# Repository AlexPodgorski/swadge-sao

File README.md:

# CR123A SAO

This is an evaluation board to test the viability of using LiMnO2 CR123A cells in a 1P3S configuration on the Swadge.

Attendees are reporting that their Swadges are too heavy. This is largely due to the 3xAA batteries, 24g each, used to power the Swadge in a 1P3S configuration. Batteries were evaluated, and CR123A batteries were selected for further evaluation on the SAO. They weigh in at 17g each.

CR123A are non-rechargeable, Lithium Chemistry batteries commonly used in camera and firearm accessory applications. They have a higher C rating than other traditional batteries (thanks to the Lithium Chemistry) and are safer than a traditional Lithium Ion or Lithium Polymer rechargeable battery. They maintain a steady voltage level of ~2.9V and discharge curves suggest approximately a 12hr battery life at 100mA continuous draw.

Preliminary testing showed:
1. Big Bug was pulling ~225mA
2. Swadge hero ~90% brightness with light show ~100mA
3. Main menu ~90mA-100mA

This is with the MT3410 + 5V USB input. 225mA at 5V is a whopping 1.125W. If we assume that same power draw and change to a 1P3S 9.0V source, we should expect to see 125mA draw (1.125W/9.0V) from the 3 cells.

The MT3410 does not support inputs above 6V, so a new DC-DC converter needed to be specified. XIAN Aerosemi Tech has other PMICs for higher voltages; the most affordable one appropriate for our use case is the <a href="https://www.lcsc.com/datasheet/lcsc_datasheet_2408140941_XI-AN-Aerosemi-Tech-MT2492_C89358.pdf">MT2492</a>. 

The MT2492 operates at a different switching frequency than the MT2410. The MT2410 switches at 1.2MHz vs 600kHz at the MT2492. I have EMI concerns with this. Additionally, the manufacturer recommends upsizing the inductor under light load conditions (<100mA), which can also impact EMI. I dont know if this will be worse, but it will be different. Predicting its behavior will be hard, so Im just going to send it on this SAO and see what happens. I have broken out the inductor pads such that I can easily drop in a new one if Id like to evaluate different values or if I need to probe something. I started with 4.7uH.

A lower switching frequency may be more efficient; I reviewed some <a href="https://www.ti.com/lit/an/slvaed3a/slvaed3a.pdf?ts=1744087588249&ref_url=https%253A%252F%252Fwww.google.com%252F"> documentation from TI </a> discussing how switching frequency impacts the performance of a buck converter. TI offers a device with adjustable switching frequency between 600kHz and 1MHz, and showed that at all loads, the 600kHz configuration ran cooler and saw ~85% efficiency vs 70% at loads we typically see in the Swadge. This is fairly device specific, but comparison of the Aerosemi datasheets suggests a higher efficiency as well with the 600kHz chip. Frankly, the plots on the datasheets are horrible and make drawing conclusions difficult. The MT2492 datasheet suggests that efficiency of the IC is around 95% at 9V/1A, and efficiency drops to around 93% at lower loads (~200mA). The MT2410 peaks at around 93% at 5V/300mA, and floats around 85% at 200mA. So, I am expecting about an 8-10% increase in efficiency switching to the MT2492.

The drawback in switching to a 600kHz solution is the requirement to upsize capacitors and inductors, which increases PCB area required for the MT2492. Higher frequency switching converters perform better in transient testing, so the MT2492 may over/undershoot during transition states more than the MT3410 does; possibly 15mV more? This is why larger capacitors and inductors are required.

A shunt Diode is in parallel with each battery into the MT2492 circuit. This is the only battery management system on board. It is possible (but unwise) to put in the RCR123A batteries (rechargeable Lithium Ion) although they have the same form factor, as there is no individual cell monitoring on this board.

# Testing Plan

The testing plan for this SAO is in two phases.

First is to attach it to a Hot Dog and monitor current draw from the USB on the SAO. This is to accomplish two tasks:
1. Compare against the existing Swadge circuit to evaluate power efficiency and noise of this new voltage regulation circuit
2. Gather more benchmark data to evaluate the battery performance

The states to be evaluated are:

1. Idle on Main Menu at max LED and TFT brightness, no screensaver
2. Big Bug at max brightness, maximum volume, general gameplay for 30 minutes and logging current consumption approximately every 60 seconds
3. Colorchord at 7 gain, LED 8, Max Screen Brightness Rainbow
4. Stepwise 0-7 TFT brightness on Main Menu
5. Stepwise 0-8 LED brightness on Main Menu
6. UTTT Wireless Connect Menu at max LED and TFT brightness

In theory, this will help us characterize current draw in various Swadge modes and help estimate run time in hours.

Second is to install the batteries and:
1. Monitor and log voltage at the diode node to GND over time
2. Monitor and log cell voltage at each node to GND over time

This will discharge a few sets of CR123A batteries in a few different states to characterize their charge time and see if the cells are staying relatively balanced. The states evaluated will be:
1. Big Bug at max brightness, maximum volume, general gameplay
2. Idle on Main Menu at max LED and TFT brightness, no screensaver
3. UTTT Wireless Connect Menu at max LED and TFT brightness

Durations for these tasks will be chosen based on the results of the first set of tests.

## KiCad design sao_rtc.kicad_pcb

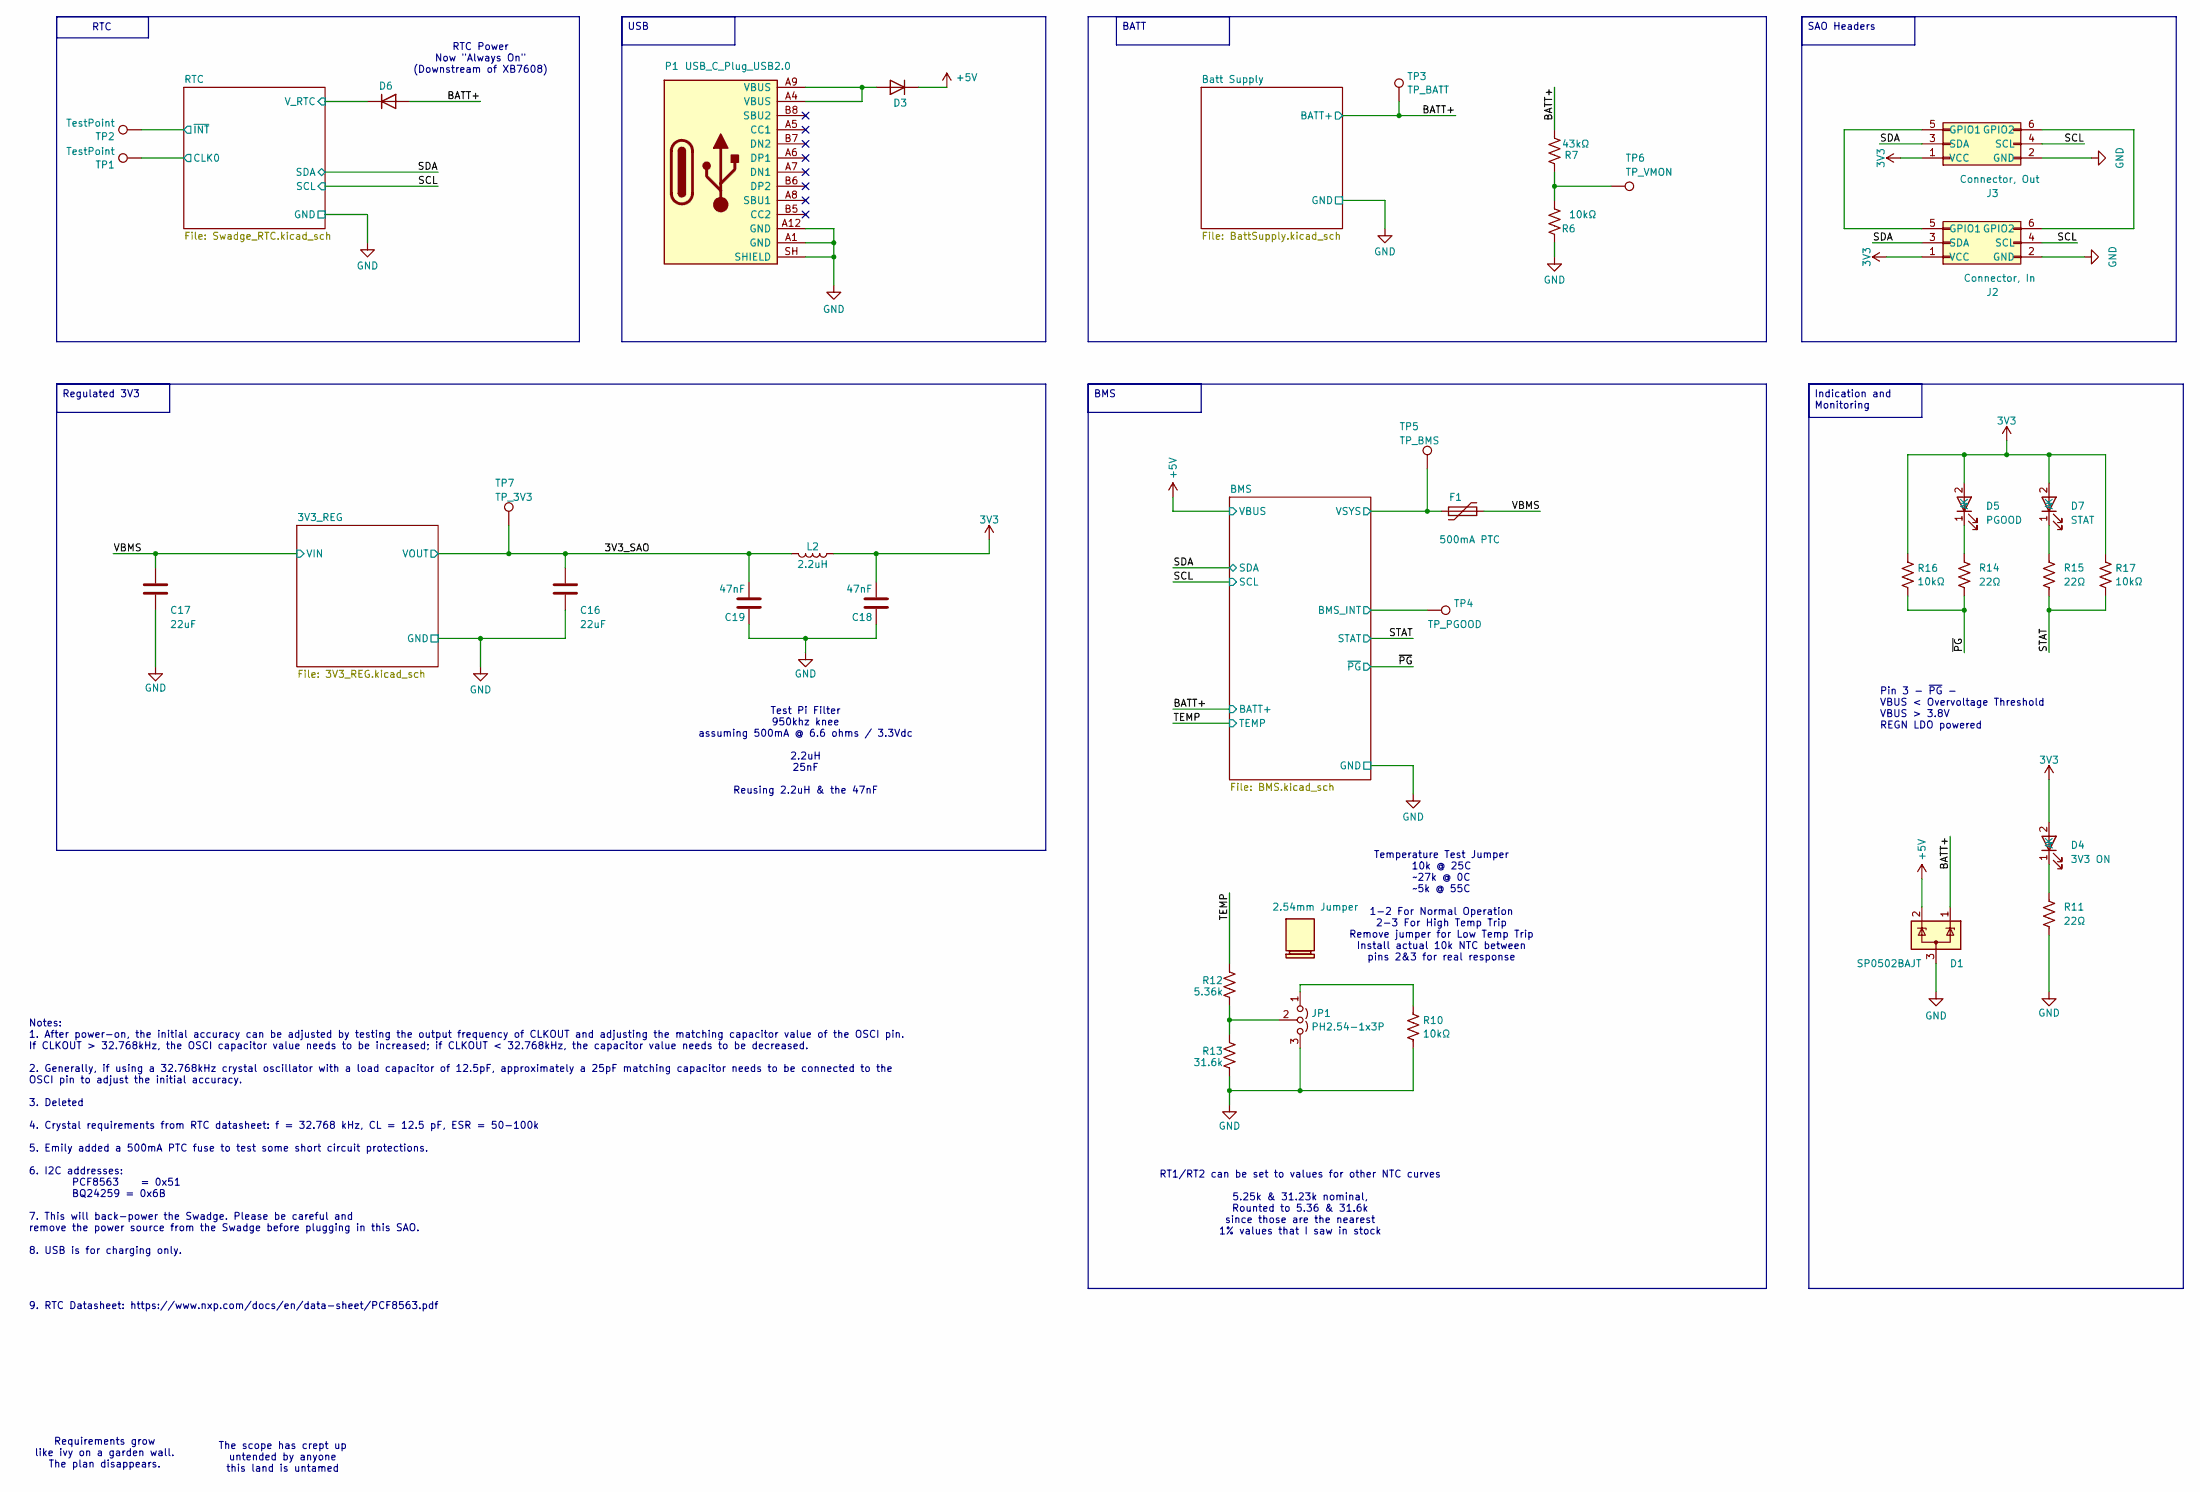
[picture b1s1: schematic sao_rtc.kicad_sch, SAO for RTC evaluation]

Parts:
C16, C17: 22uF; C_0603_1608Metric; LCSC C77042
C18, C19: 47nF; C_0603_1608Metric; LCSC C107093
D1: SP0502BAJT; SOT-323_SC-70; LCSC C207262
D3, D6: D; D_SMA; Digikey 2616-GS1J-ND
D4: 3V3 ON; LED_0603_1608Metric; LCSC C965804
D5: PGOOD; LED_0603_1608Metric; LCSC C965804
D7: STAT; LED_0603_1608Metric; LCSC C965804
F1: 500mA PTC; Fuse_0805_2012Metric
H1: 2.54mm Jumper; LCSC C5305
J2: Connector, In; PinHeader_2x03_P2.54mm_Vertical; LCSC C492420
J3: Connector, Out; PinHeader_2x03_P2.54mm_Vertical_Flipped; LCSC C541853
JP1: PH2.54-1x3P; PinHeader_1x03_P2.54mm_Vertical; LCSC C42431836
L2: 2.2uH; L_1008_2520Metric; LCSC C216158
P1: USB_C_Plug_USB2.0; USB_C_Receptacle_HRO_TYPE-C-31-M-12; LCSC C2765186
R6, R10, R16, R17: 10kΩ; R_0603_1608Metric; LCSC C25804
R7: 43kΩ; R_0603_1608Metric; LCSC C23172
R11, R14, R15: 22Ω; R_0603_1608Metric; LCSC C23345
R12: 5.36k; R_0603_1608Metric; LCSC C25973
R13: 31.6k; R_0603_1608Metric; LCSC 25967
TP1, TP2: TestPoint; TestPoint_Loop_D2.60mm_Drill1.4mm_Beaded; LCSC C5199801
TP3: TP_BATT; TestPoint_Loop_D2.60mm_Drill1.4mm_Beaded; LCSC C5199801
TP4: TP_PGOOD; TestPoint_Loop_D2.60mm_Drill1.4mm_Beaded; LCSC C5199801
TP5: TP_BMS; TestPoint_Loop_D2.60mm_Drill1.4mm_Beaded; LCSC C5199801
TP6: TP_VMON; TestPoint_Loop_D2.60mm_Drill1.4mm_Beaded; LCSC C5199801
TP7: TP_3V3; TestPoint_Loop_D2.60mm_Drill1.4mm_Beaded; LCSC C5199801

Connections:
3V3: C18.1, D4.2 (A), D5.2 (A), D7.2 (A), J2.1 (VCC), J3.1 (VCC), L2.1, R16.2, R17.2
+5V: D1.2 (K), D3.1 (K); also elsewhere on the board
/3V3_SAO: C16.1, C19.1, L2.2, TP7.1 (1_1); also elsewhere on the board
/BATT+: D1.1 (K), D6.2 (A), R7.2, TP3.1 (1_1); also elsewhere on the board
/BMS/BMS_INT: TP4.1 (1_1); also elsewhere on the board
/BMS/VSYS: F1.1, TP5.1 (1_1); also elsewhere on the board
/RTC/CLK0: TP1.1 (1_1); also elsewhere on the board
/RTC/V_RTC: D6.1 (K); also elsewhere on the board
/RTC/~INT: TP2.1 (1_1); also elsewhere on the board
/SCL: J2.4 (SCL), J3.4 (SCL); also elsewhere on the board
/SDA: J2.3 (SDA), J3.3 (SDA); also elsewhere on the board
/STAT: R15.1, R17.1; also elsewhere on the board
/TEMP: R12.1; also elsewhere on the board
/VBMS: C17.1, F1.2; also elsewhere on the board
/~PG: R14.1, R16.1; also elsewhere on the board
GND: C16.2, C17.2, C18.2, C19.2, D1.3 (A), J2.2 (GND), J3.2 (GND), JP1.3 (B), P1.A1 (GND), P1.A12 (GND), P1.SH (SHIELD), R6.2, R10.1, R11.1, R13.2; also elsewhere on the board
unnamed: D3.2 (A), P1.A4 (VBUS), P1.A9 (VBUS)
unnamed: D4.1 (K), R11.2
unnamed: D5.1 (K), R14.2
unnamed: D7.1 (K), R15.2
unnamed: J2.5 (GPIO1), J3.5 (GPIO1)
unnamed: J2.6 (GPIO2), J3.6 (GPIO2)
unnamed: JP1.1 (A), R10.2
unnamed: JP1.2 (C), R12.2, R13.1
unnamed: R6.1, R7.1, TP6.1 (1_1)

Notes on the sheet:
Test Pi Filter 950khz knee assuming 500mA @ 6.6 ohms / 3.3Vdc 2.2uH 25nF Reusing 2.2uH & the 47nF
The scope has crept up untended by anyone this land is untamed
RTC
Temperature Test Jumper 10k @ 25C ~27k @ 0C ~5k @ 55C 1-2 For Normal Operation 2-3 For High Temp Trip Remove jumper for Low Temp Trip Install actual 10k NTC between pins 2&3 for real response
RT1/RT2 can be set to values for other NTC curves 5.25k & 31.23k nominal, Rounted to 5.36 & 31.6k since those are the nearest 1% values that I saw in stock
Requirements grow like ivy on a garden wall. The plan disappears.
9. RTC Datasheet: https://www.nxp.com/docs/en/data-sheet/PCF8563.pdf
Notes: 1. After power-on, the initial accuracy can be adjusted by testing the output frequency of CLKOUT and adjusting the matching capacitor value of the OSCI pin. If CLKOUT > 32.768kHz, the OSCI capacitor value needs to be increased; if CLKOUT < 32.768kHz, the capacitor value needs to be decrease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
Pin 3 - ~{PG} - VBUS < Overvoltage Threshold VBUS > 3.8V REGN LDO powered
RTC Power Now "Always On" (Downstream of XB7608)
SAO Headers
BATT
BMS
USB
Indication and Monitoring
Regulated 3V3

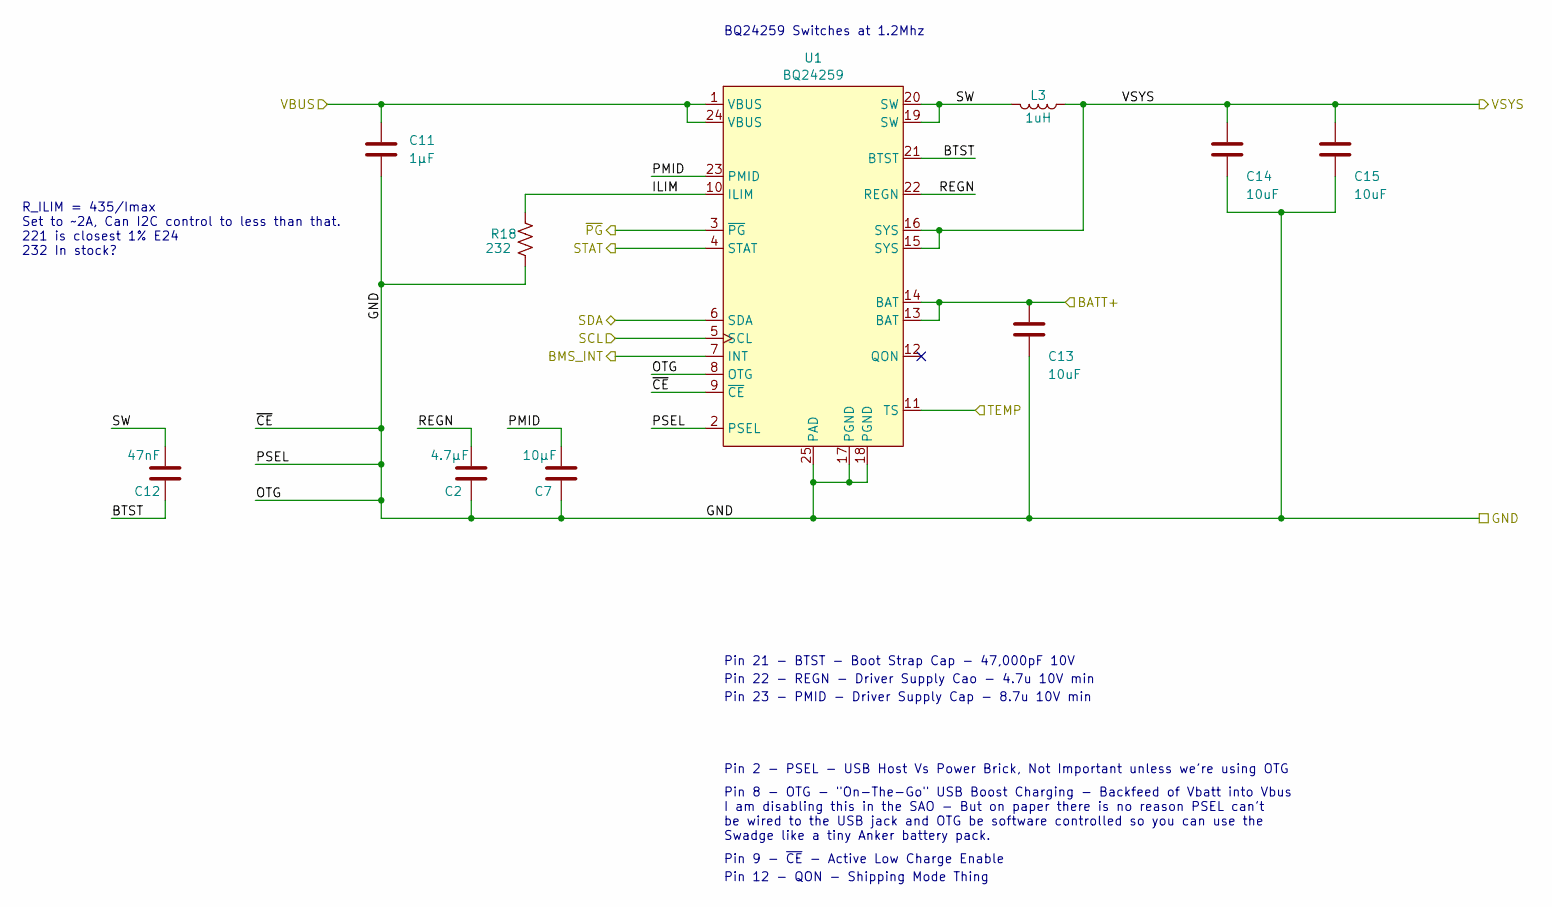
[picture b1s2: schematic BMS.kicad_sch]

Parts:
C2: 4.7μF; C_0603_1608Metric; LCSC C1705
C7: 10μF; C_0603_1608Metric; LCSC C85713
C11: 1μF; C_0603_1608Metric; LCSC C159801
C12: 47nF; C_0603_1608Metric; LCSC C107093
C13, C14, C15: 10uF; C_0603_1608Metric; LCSC C1691
L3: 1uH; L_1008_2520Metric; LCSC C48996586
R18: 232; R_0603_1608Metric; LCSC C23009
U1: BQ24259; HVQFN-24-1EP_4x4mm_P0.5mm_EP2.6x2.6mm_ThermalVias; LCSC C473366

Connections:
+5V: C11.1, U1.1 (VBUS), U1.24 (VBUS); also elsewhere on the board
/BATT+: C13.1, U1.13 (BAT), U1.14 (BAT); also elsewhere on the board
/BMS/BMS_INT: U1.7 (INT); also elsewhere on the board
/BMS/BTST: C12.2, U1.21 (BTST)
/BMS/ILIM: R18.1, U1.10 (ILIM)
/BMS/PMID: C7.1, U1.23 (PMID)
/BMS/REGN: C2.1, U1.22 (REGN)
/BMS/SW: C12.1, L3.2, U1.19 (SW), U1.20 (SW)
/BMS/VSYS: C14.1, C15.1, L3.1, U1.15 (SYS), U1.16 (SYS); also elsewhere on the board
/SCL: U1.5 (SCL); also elsewhere on the board
/SDA: U1.6 (SDA); also elsewhere on the board
/STAT: U1.4 (STAT); also elsewhere on the board
/TEMP: U1.11 (TS); also elsewhere on the board
/~PG: U1.3 (~PG); also elsewhere on the board
GND: C2.2, C7.2, C11.2, C13.2, C14.2, C15.2, R18.2, U1.2 (PSEL), U1.8 (OTG), U1.9 (~CE), U1.17 (PGND), U1.18 (PGND), U1.25 (PAD); also elsewhere on the board

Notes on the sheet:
Pin 9 - ~{CE} - Active Low Charge Enable
Pin 21 - BTST - Boot Strap Cap - 47,000pF 10V
R_ILIM = 435/Imax Set to ~2A, Can I2C control to less than that. 221 is closest 1% E24 232 In stock?
Pin 2 - PSEL - USB Host Vs Power Brick, Not Important unless we're using OTG
Pin 23 - PMID - Driver Supply Cap - 8.7u 10V min
BQ24259 Switches at 1.2Mhz
Pin 12 - QON - Shipping Mode Thing
Pin 8 - OTG - "On-The-Go" USB Boost Charging - Backfeed of Vbatt into Vbus I am disabling this in the SAO - But on paper there is no reason PSEL can't be wired to the USB jack and OTG be software controlled so you can use the Swadge like a tiny Anker battery pack.
Pin 22 - REGN - Driver Supply Cao - 4.7u 10V min

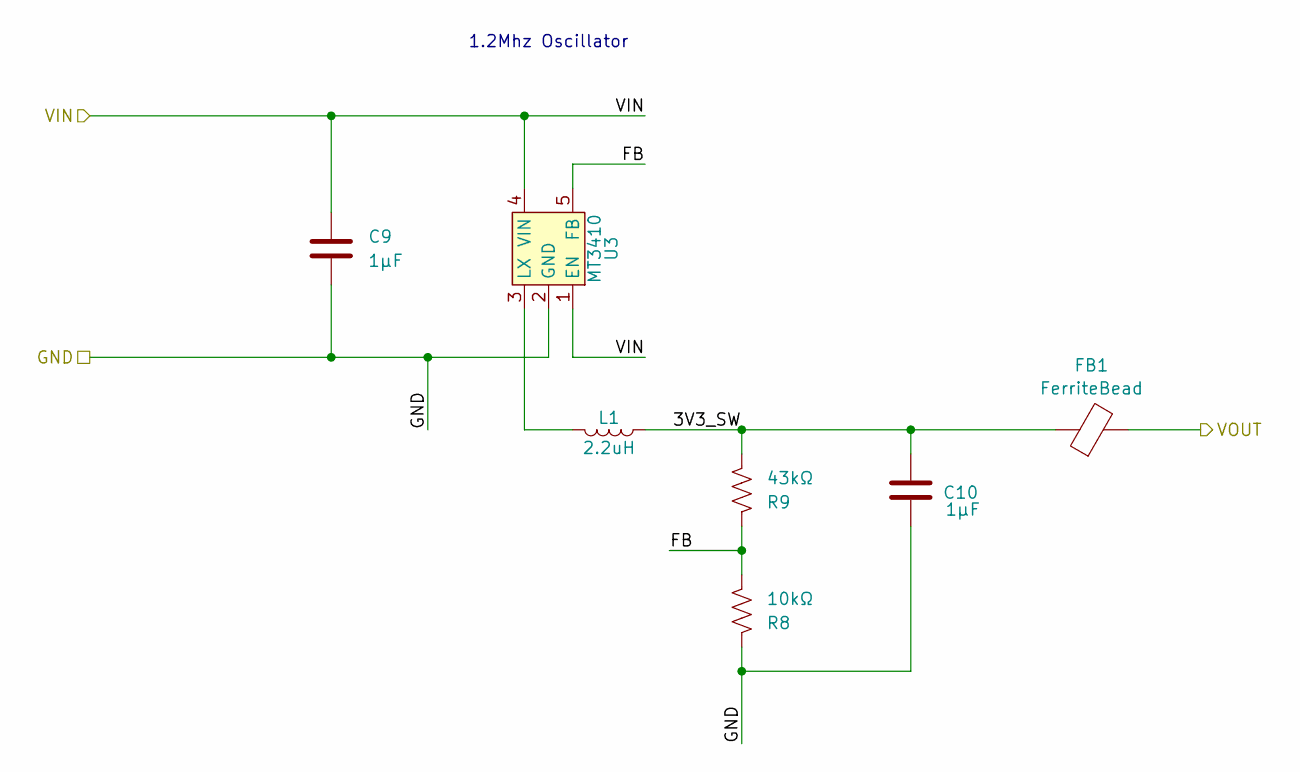
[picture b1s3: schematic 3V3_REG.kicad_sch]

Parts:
C9: 1μF; C_0603_1608Metric; LCSC C159801
C10: 1μF; C_0603_1608Metric; LCSC C15849
FB1: FerriteBead; L_TDK_NLV32_3.2x2.5mm; LCSC C237479
L1: 2.2uH; L_1008_2520Metric; LCSC C216158
R8: 10kΩ; R_0603_1608Metric; LCSC C25804
R9: 43kΩ; R_0603_1608Metric; LCSC C23172
U3: MT3410; SOT-23-5; LCSC C42420805

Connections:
/3V3_REG/3V3_SW: C10.1, FB1.1, L1.1, R9.2
/3V3_REG/FB: R8.2, R9.1, U3.5 (FB)
/3V3_SAO: FB1.2; also elsewhere on the board
/VBMS: C9.1, U3.1 (EN), U3.4 (VIN); also elsewhere on the board
GND: C9.2, C10.2, R8.1, U3.2 (GND); also elsewhere on the board
unnamed: L1.2, U3.3 (LX)

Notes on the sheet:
1.2Mhz Oscillator

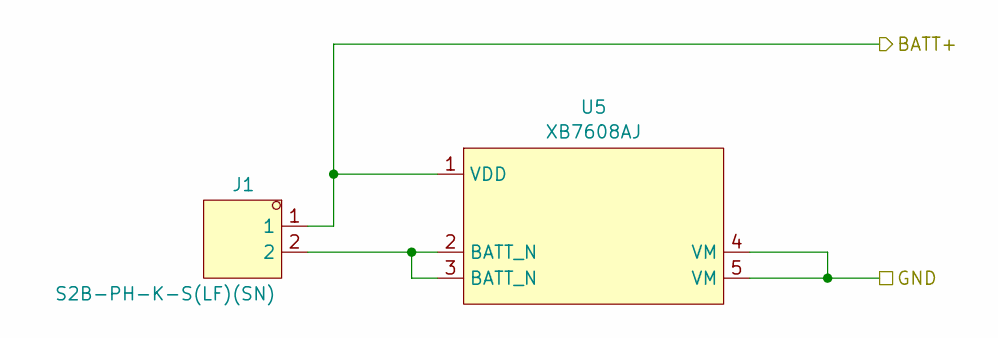
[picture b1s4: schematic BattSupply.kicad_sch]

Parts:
J1: S2B-PH-K-S(LF)(SN); PinHeader_1x02_P2.00mm_Horizontal; LCSC C173752
U5: XB7608AJ; CPC-5_2.6mmx4mm_P0.53mm; LCSC C2681921

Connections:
/BATT+: J1.1, U5.1 (VDD); also elsewhere on the board
GND: U5.4 (VM), U5.5 (VM); also elsewhere on the board
unnamed: J1.2, U5.2 (BATT_N), U5.3 (BATT_N)

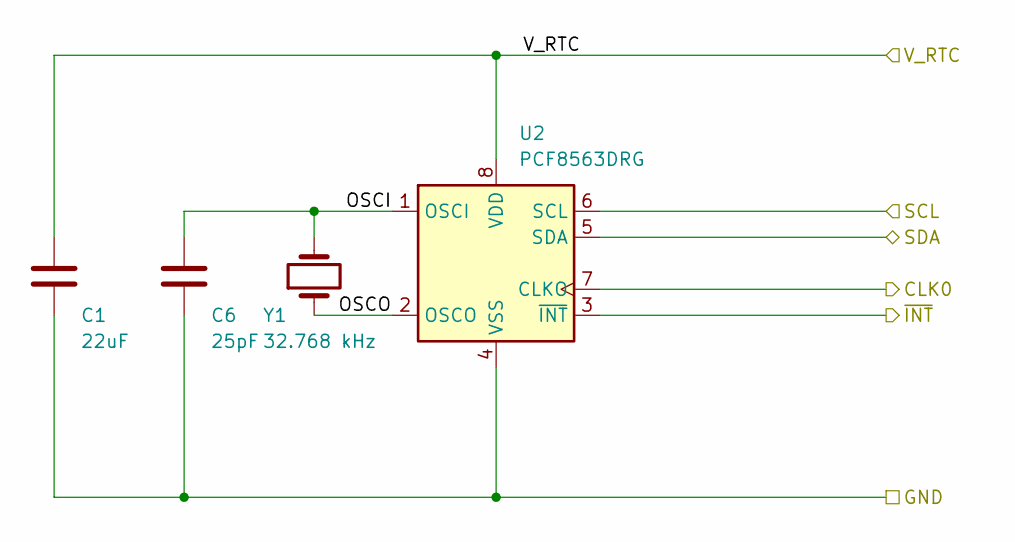
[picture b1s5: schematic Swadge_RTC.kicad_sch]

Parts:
C1: 22uF; C_0603_1608Metric; LCSC C77042
C6: 25pF; C_0603_1608Metric; LCSC C282067
U2: PCF8563DRG; SOIC-8_3.9x4.9mm_P1.27mm; LCSC C42396735
Y1: 32.768 kHz; Crystal_SMD_3215-2Pin_3.2x1.5mm; LCSC C32346

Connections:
/RTC/CLK0: U2.7 (CLKO); also elsewhere on the board
/RTC/OSCI: C6.1, U2.1 (OSCI), Y1.2
/RTC/OSCO: U2.2 (OSCO), Y1.1
/RTC/V_RTC: C1.1, U2.8 (VDD); also elsewhere on the board
/RTC/~INT: U2.3 (~INT); also elsewhere on the board
/SCL: U2.6 (SCL); also elsewhere on the board
/SDA: U2.5 (SDA); also elsewhere on the board
GND: C1.2, C6.2, U2.4 (VSS); also elsewhere on the board

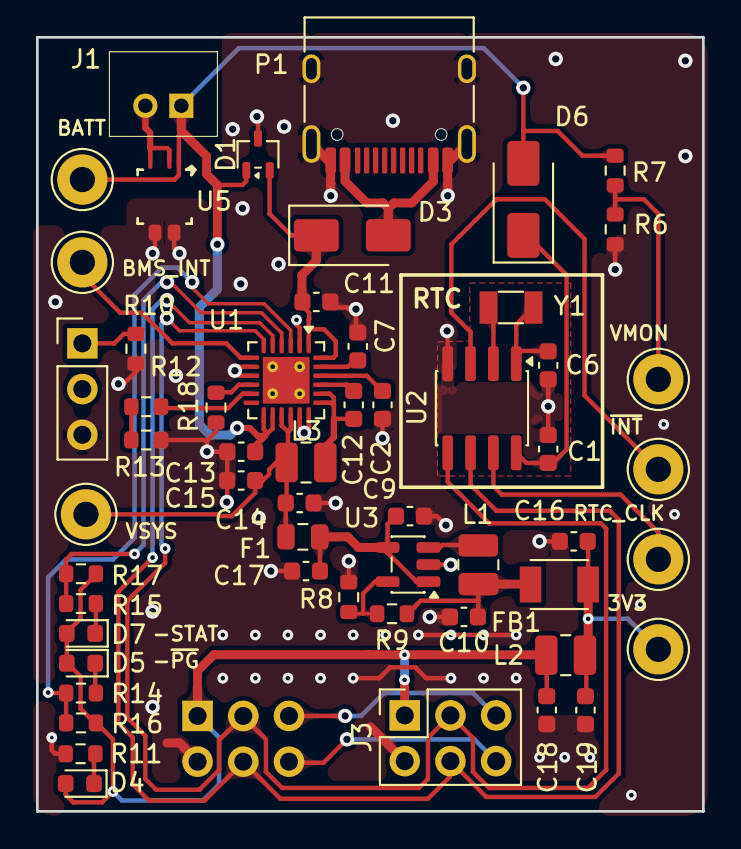
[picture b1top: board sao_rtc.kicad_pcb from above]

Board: 2 copper layers, 37.0 x 43.0 mm, 56 parts (1 on the bottom side), 36 nets.

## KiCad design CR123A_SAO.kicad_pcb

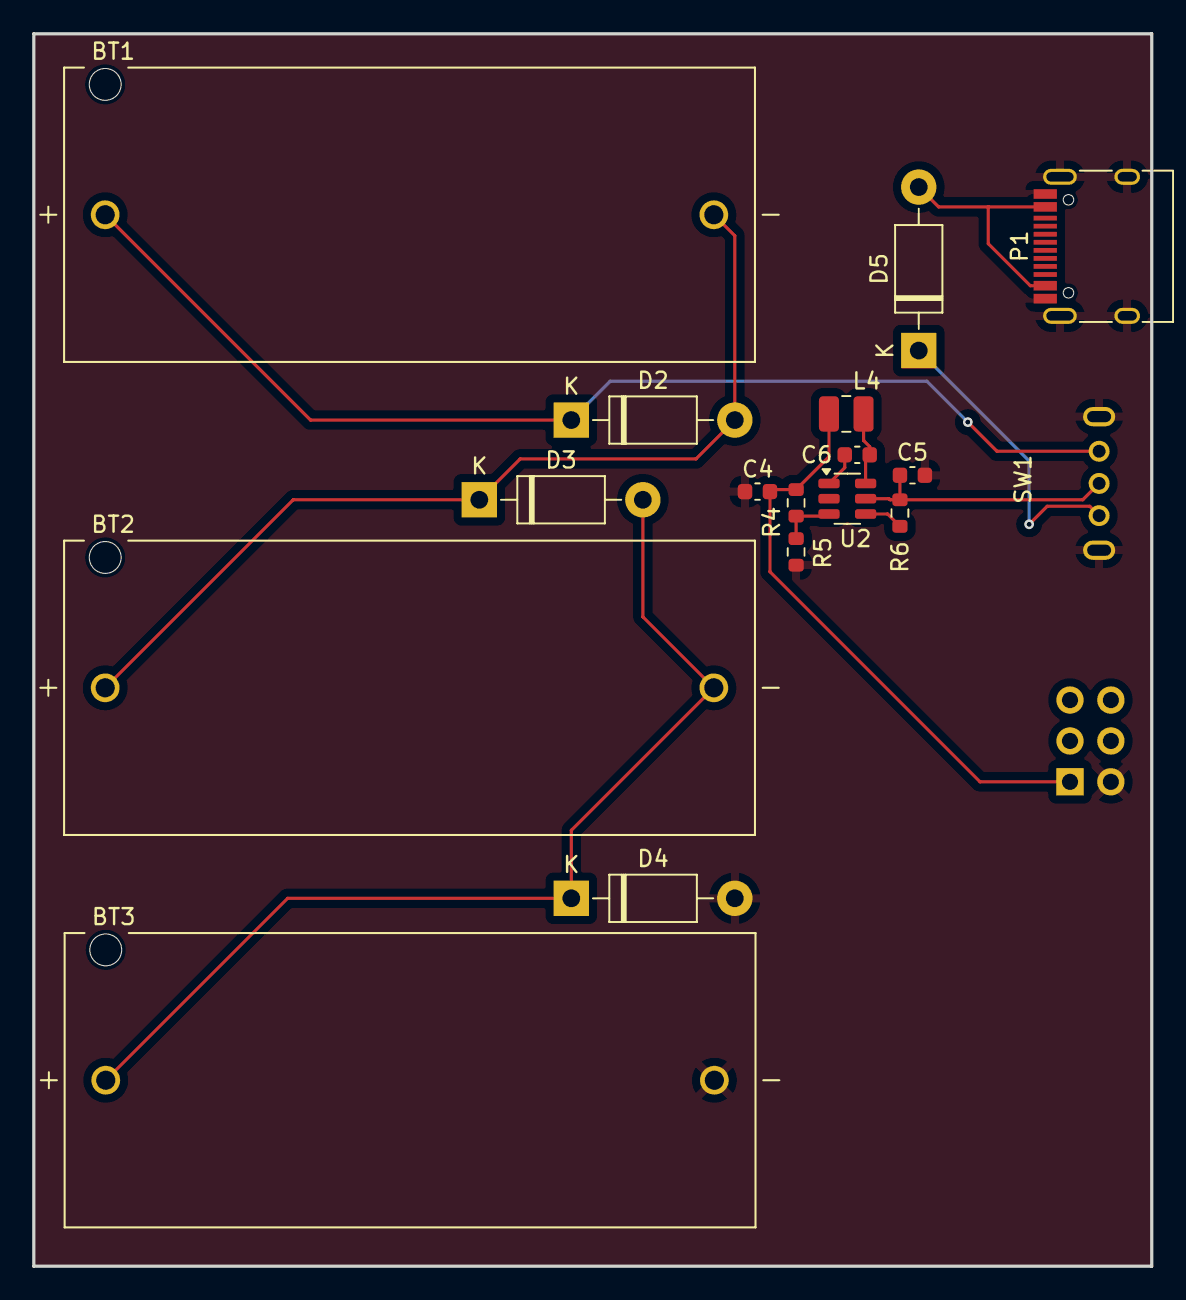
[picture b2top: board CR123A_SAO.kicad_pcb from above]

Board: 2 copper layers, 69.5 x 76.6 mm, 18 parts (1 on the bottom side), 12 nets.

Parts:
BT1, BT2, BT3: 1051; BAT_1051
C4, C5: 22μF; C_0603_1608Metric
C6: 22nF; C_0603_1608Metric
D2, D3, D4, D5: 1N5817; D_DO-41_SOD81_P10.16mm_Horizontal
J1: Conn_02x03_Odd_Even; PinHeader_2x03_P2.54mm_Vertical
L4: 4.7uH; L_1008_2520Metric
P1: USB_C_Plug_USB2.0; USB_C_Receptacle_HRO_TYPE-C-31-M-12
R4: 36k; R_0603_1608Metric
R5, R6: 8k; R_0603_1608Metric
SW1: SW_SPDT_1825232-1; 1825232-1
U2: MT2492; SOT-23-6

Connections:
+5V: D5.1 (K), SW1.1 (A)
+9V: BT1.P, D2.1 (K), SW1.3 (C)
GND: BT3.N, C4.2, C5.2, D4.2 (A), J1.2 (GND), P1.A1_B12 (GND), P1.A12_B1 (GND), P1.S1 (SHIELD), R5.2, SW1.4 (D), SW1.5 (E), U2.2 (GND)
unnamed: BT1.N, BT2.P, D2.2 (A), D3.1 (K)
unnamed: BT2.N, BT3.P, D3.2 (A), D4.1 (K)
unnamed: D5.2 (A), P1.A4_B9 (VBUS), P1.A9_B4 (VBUS)
unnamed: C6.2, U2.1 (BS)
unnamed: R6.2, U2.4 (EN)
unnamed: R4.2, R5.1, U2.3 (FB)
unnamed: C6.1, L4.2, U2.6 (SW)
VCC: C4.1, J1.1 (VCC), L4.1, R4.1
VDC: C5.1, R6.1, SW1.2 (B), U2.5 (IN)

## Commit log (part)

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2025-04-07 cr123a sao
    to evaluate different power solution
2025-04-07 documentation makes the world go round
2025-04-07 Update README.md
    html hard
2025-04-10 ADDING MT2492
2025-04-10 redo layout
2025-04-11 sent to jlcpcb
2026-05-29 SAO RTC
2026-05-29 add sch and pcb
2026-05-29 file cleanup
2026-05-29 scope creep is a hell of a drug
    Add AW320001 BMS and associated stuff
2026-06-01 update schematic for voltage regulation
    she creeped my scope until I swadged her
2026-06-03 routed and ordered
2026-06-04 adjust low pass filter
    change LC values for part sourcing
